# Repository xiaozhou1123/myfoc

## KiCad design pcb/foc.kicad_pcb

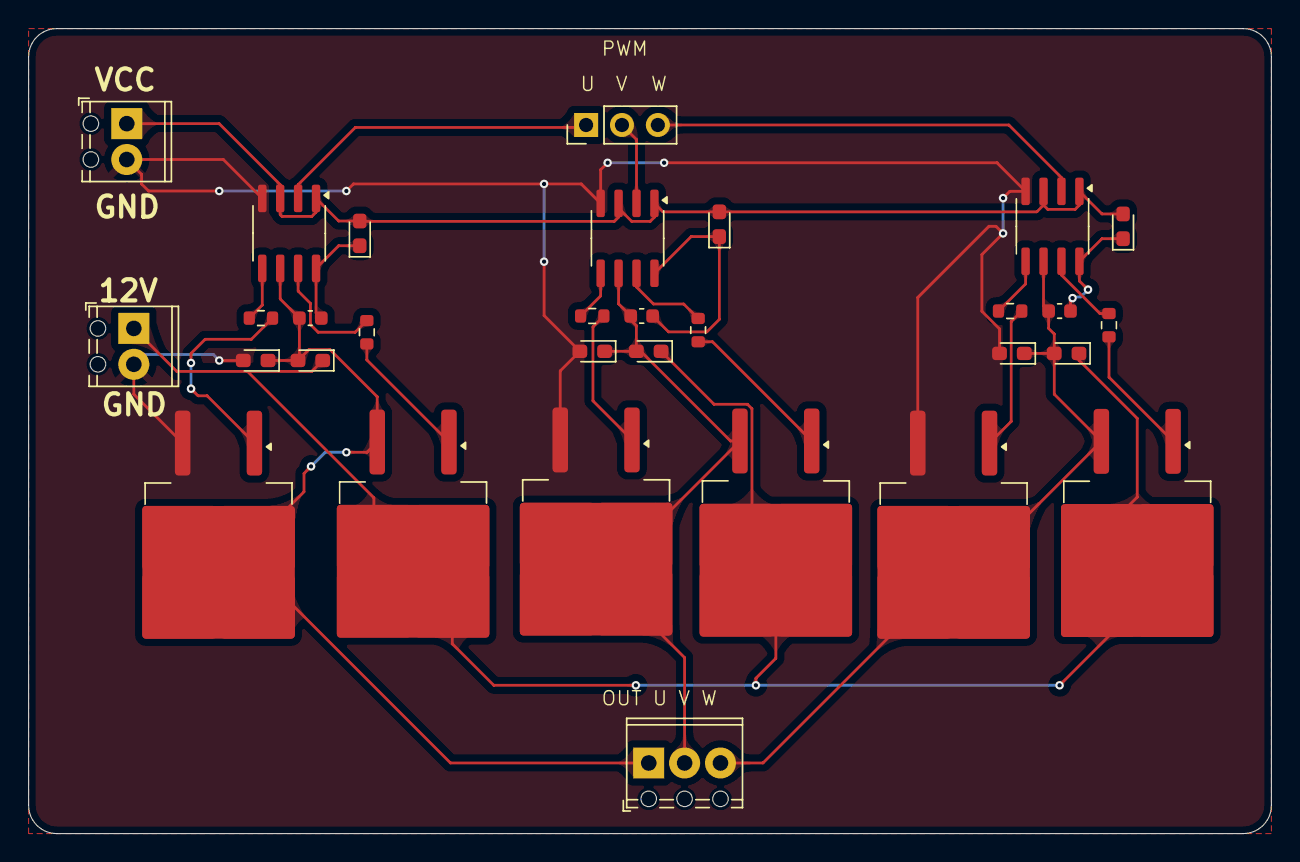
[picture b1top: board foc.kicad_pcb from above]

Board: 2 copper layers, 88.0 x 57.0 mm, 31 parts (0 on the bottom side), 24 nets.

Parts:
C1, C4, C6: 10uF; C_0603_1608Metric
D1, D2, D3, D4, D5, D6, D7, D8, D9: D; D_0603_1608Metric_Pad1.05x0.95mm_HandSolder
J1: TerminalBlock_Phoenix_MPT-0,5-3-2.54_1x03_P2.54mm_Horizontal
J2, J3: Conn_01x02; TerminalBlock_Phoenix_MPT-0,5-2-2.54_1x02_P2.54mm_Horizontal
J4: Conn_01x03; PinHeader_1x03_P2.54mm_Vertical
Q1, Q2, Q3, Q4, Q5, Q6: IRF3205; TO-263-2
R1, R2, R3, R4, R5, R6: 30R; R_0603_1608Metric
U1, U2, U3: IR2104; SOIC-8_3.9x4.9mm_P1.27mm

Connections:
+12V: D2.1 (K), D5.1 (K), D8.1 (K), J3.1, Q1.2 (D), Q3.2 (D), Q5.2 (D)
/MOTOR_U: C1.1, D2.2 (A), D3.1 (K), J1.1, Q1.3 (S), Q2.2 (D), U1.6 (VS)
/MOTOR_V: C4.1, D5.2 (A), D6.1 (K), J1.2, Q3.3 (S), Q4.2 (D), U2.6 (VS)
/MOTOR_W: C6.1, D8.2 (A), D9.1 (K), J1.3, Q5.3 (S), Q6.2 (D), U3.6 (VS)
/PWM_U: J4.1, U1.2 (IN)
/PWM_V: J4.2, U2.2 (IN)
/PWM_W: J4.3, U3.2 (IN)
GND: D3.2 (A), D6.2 (A), D9.2 (A), J2.2, J3.2, Q2.3 (S), Q4.3 (S), Q6.3 (S), U1.4 (COM), U2.4 (COM), U3.4 (COM)
unnamed: C1.2, D1.1 (K), U1.8 (VB)
unnamed: C4.2, D4.1 (K), U2.8 (VB)
unnamed: C6.2, D7.1 (K), U3.8 (VB)
unnamed: Q1.1 (G), R1.2
unnamed: Q2.1 (G), R2.2
unnamed: Q3.1 (G), R3.2
unnamed: Q4.1 (G), R4.2
unnamed: Q5.1 (G), R5.2
unnamed: Q6.1 (G), R6.2
unnamed: R1.1, U1.7 (HO)
unnamed: R2.1, U1.5 (LO)
unnamed: R3.1, U2.7 (HO)
unnamed: R4.1, U2.5 (LO)
unnamed: R5.1, U3.7 (HO)
unnamed: R6.1, U3.5 (LO)
VCC: D1.2 (A), D4.2 (A), D7.2 (A), J2.1, U1.1 (VCC), U1.3 (~SD), U2.1 (VCC), U2.3 (~SD), U3.1 (VCC), U3.3 (~SD)

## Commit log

2024-05-28 README
2024-05-29 update pcb
